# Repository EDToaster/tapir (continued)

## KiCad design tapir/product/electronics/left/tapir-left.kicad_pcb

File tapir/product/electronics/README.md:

# Tapir Rev A | electrical handoff

Open `left/tapir-left.kicad_pro` and `right/tapir-right.kicad_pro` separately in **KiCad 10.0.8**. These are physically distinct two-layer carriers, not the same PCB flipped over. The native schematics, boards, editable libraries, component STEP files and local tables live together here. Nothing in this directory is a purchase, fabrication or assembly authorization.

## What is on the carrier

| Circuit | Left | Right | Electrical contract |
|---|---:|---:|---|
| SW1–21 + D1–21 | 21 | 21 | Direct-solder Kailh CPG135001D01. P1 = column, P2 = corresponding diode anode; diode pad 1/cathode returns to ROW. One diode per physical switch. |
| SW22–24 + D22–24 | 3 | 0 | PTS810SJM250SMTR LFS. R3C0 = left click; R3C1 = scroll hold; R3C2 = right click. Thumb keys remain R3C3/4/5, outer to inner. |
| U1 | 1 | 1 | [Seeed XIAO nRF52840 Plus, non-Sense](https://www.seeedstudio.com/Seeed-Studio-XIAO-nRF52840-Plus-p-6359.html), 102010672. Surface-mount the module, including its underside pads. Header-mounted or non-Plus boards do not implement this carrier. |
| J1, S1 | 1 each | 1 each | [Protected 100 mAh pack](https://www.adafruit.com/product/1570); factory PH termination, no cutting or battery soldering. J1.1 = CELL_PLUS, J1.2 = GND. S1.2 = cell, S1.1 = VBAT_SW, S1.3 = isolated. |
| U2, C1, C2, R1–R3, J2 | 0 | 1 each | [Active-high TPS22918DBVR](https://www.ti.com/product/TPS22918) switches the pointer's 3.3 V rail. The Sprintek driver and head are an **off-board harness assembly**, not fake components placed on the main PCB. |

Every switch row uses the same scan polarity. Local columns run outer to inner on both hands; firmware reverses the right physical column order when forming the Corne logical layout. The matrix path is COL → switch → diode A → diode K → ROW. The left mouse controls are physical, diode-isolated inputs, not overloaded key combinations.

### Module interface

| Carrier U1 pads | Module pins | Use |
|---|---|---|
| 1, 2, 3, 4 | D0…D3 | ROW0…ROW3 |
| 5, 6, 7, 8, 9, 10 | D4…D9 | COL0…COL5 |
| 11, 15, 16, 17 | D10/P1.15, D11/P0.15, D12/P0.19, D13/P1.01 | Right: PS2_DATA, PS2_CLK, PS2_RST, PTR_EN. Left: intentionally unused. |
| 12, 13, 14 | 3V3, ground, VBUS | U1.12 supplies only the right pointer circuit. No carrier VBUS load; USB data, ESD, connector and charger are on U1. |
| 18–23 | D14…D19 | All intentionally unused. D14/15 are shared with NFC; D16 is a battery-sense pin. |
| 24, 25, 26, 27 | SWDIO, SWDCLK, nRESET, ground | First three are unused host pads; 27 is connected to carrier GND. Use the module button for recovery, removing the right bridge with the cell disconnected. No side-access SWD header is claimed. |
| 28, 29 | BAT+, BAT− | VBAT_SW and GND. These are invisible once the XIAO is installed: confirm land overlap, paste transfer and solder quality on a coupon/sample before accepting assembly. |

Numbering is the **host footprint**, not the GPIO number. The [Seeed Plus board artwork](https://files.seeedstudio.com/wiki/XIAO-BLE/Seeed_Studio_XIAO_nRF52840_Plus.zip), [host land pattern](https://files.seeedstudio.com/wiki/XIAO-KiCad-Library/New_XIAO_Series_Footprints.zip) and [Zephyr Plus pin table](https://docs.zephyrproject.org/latest/boards/seeed/xiao_nrf52840_plus/doc/index.html) are the basis. The host battery lands are not exactly centered on the module's actual rectangles: see `reports/xiao-hidden-lands.json` for the explicit geometry comparison. That is a land-overlap audit, not inspection of a solder joint.

### Power and pointing assembly

S1 disconnects **the cell**, not USB. Switch open + cable attached means the MCU can still run and the cell cannot charge. With S1 closed the module's onboard charger is connected to the cell. Do not fit an additional charger or assume that the mere presence of pack protection makes an unknown charge setting safe. [Seeed specifies high-impedance P0.13 without pulls for approximately 50 mA](https://wiki.seeedstudio.com/XIAO_BLE/); check every bootloader/application startup path and measure cell current before unattended use. The [1570 pack drawing and electrical limits](https://cdn-shop.adafruit.com/product-files/1570/1570datasheet.pdf) take precedence over marketing dimensions.

**Check polarity before mating the real cell.** In the [Adafruit Feather M0 rev C PCB](https://github.com/adafruit/Adafruit-Feather-M0-Basic-Proto-PCB/blob/master/Adafruit%20Feather%20M0%20Basic%20rev%20C.brd), X1 pad 2 is VBAT and pad 1 is ground. Its Eagle XY and mating orientation differ from the [KiCad JST footprint](https://gitlab.com/kicad/libraries/kicad-footprints/-/blob/10.0.8/Connector_JST.pretty/JST_PH_S2B-PH-SM4-TB_1x02-1MP_P2.00mm_Horizontal.kicad_mod): align the **physical mating faces**, not printed pad numbers. In Tapir the left native pad (−1,−2.85) is +, the right pad (+1,−2.85) is −. Confirm the actual pack with a meter at its unplugged housing, then continuity from an unpowered mated dummy pigtail through J1/S1 to U1 pads 28/29. Do not probe by shorting adjacent live contacts. Do not connect anything if these checks disagree.

Right J2 is a row of five wire terminations, not an 8-pin FFC footprint. Read the actual **Method 1 castellated** pin-1 mark on the [Sprintek SK8707-01-004 drawing, pages 3–4](https://docs.holykeebs.com/datasheets/SK8707-01.pdf#page=3). Do not use the pin numbering of either FFC alternative.

| J2 → Sprintek Method 1 | Signal | Expected |
|---|---|---|
| 1 → 1 | GND | Common return; square pad marks carrier pin 1. |
| 2 → 2 | PS2_DATA | Open drain; 4.7 kΩ to PTR_3V3, never to unswitched 3V3. |
| 3 → 3 | PS2_CLK | Same pull-up scheme; no pull-ups enabled from the MCU when off. |
| 4 → 4 | PS2_RST | Active high. Hold low or release as appropriate; never drive high with driver VCC off. |
| 5 → 5 | PTR_3V3 | U2.6. U2.5 QOD is tied here to discharge the rail. U2.4 CT is deliberately open; R3 100 kΩ defaults EN low. |
| None → 6,7,8 | Driver mouse inputs | Not wired to the carrier or left half. |

Keep the four raw sensor-to-driver connections separate from this five-wire host cable. Fit the original matched driver/head pair from the **3.3 V detached –004** kit; maintain sensor/driver matching marks and verified wiring order. If the kit is not already terminated, label both sides of each of the four wires from the supplied sensor/driver markings or vendor guidance; do not infer pin order from a generic donor or trace color. Do not power until checked. Keep sensor wires short and strain relieved, away from switch tails, the antenna and moving parts. Insulate driver solder joints from the carrier; the separate bridge must take pointing loads. Physical retention, reach, lead dress, calibration and assembled RSSI are prototype gates.

R1/R2 draw about 0.70 mA per line, but only while that line is low and the rail is enabled. The right driver itself draws a typical [2.09 mA active, 0.65 or 1.44 mA idle depending on Z-tap, and 40 µA in its power-down mode](https://docs.holykeebs.com/datasheets/SK8707-01.pdf#page=5). U2's 1 µF input / 0.1 µF local output is a 10:1 local ratio; the module's unknown internal capacitance and cable add to the load. Scope turn-on droop, discharge, clock edges and leakage with the real assembly; do not convert these nominal figures into a measured keyboard runtime.

## Stackup, drawings and gates

Target standard **2-layer FR-4, finished 1.6 mm, 1 oz outer copper, ENIG, tented vias**; no impedance-controlled bus is routed on the carrier. Nominal signal traces are 0.20 mm, power/ground 0.30 mm, copper spacing at least 0.20 mm, copper to routed edge 0.30 mm, copper to unrelated drilled holes 0.25 mm. Through vias are 0.60/0.30 mm (signal) or 0.65/0.30 mm (power); carrier-mount NPTHs are Ø2.20 mm with Ø5.40 keepouts. These are design targets, not a board-house quote; recheck the [JLCPCB rigid production capabilities](https://jlcpcb.com/capabilities/pcb-capabilities/) and actual stack/finish/tolerance at release. Solder/paste process, panel rails, tool access, registration, coupon and drill compensation need fabrication review.

Do not mirror any offset a second time. In the PCB editor each hand uses `XY = geometry.XY + (100,100) mm`, and clockwise geometry angles become negative KiCad angles. The vendor XIAO's native USB points +X, so its exception is `rotation = 90° − geometry.a`. `step/tapir-<hand>-populated.step` uses a **100×100 mm user origin**; thus STEP XY = (geometry.x, −geometry.y) and the component seating plane is at STEP z = +1.595 mm. The exported dielectric solid is not the whole finished copper/mask stack. No detached module, bridge, battery, harness or case is pretended to exist on the native carrier STEP. See `models/` for real part versus independent fit-proxy status.

- **Electrical evidence:** `reports/tapir-<hand>-erc.json`, `...-drc.json`, `...-schematic-parity.json`, `...-routing.json`. Check report counts, `passes`, and that the board revision matches the report. Missing reports do not pass. The native DRC JSON records default advisory checks ignored by KiCad; no per-instance violations have been accepted as exclusions. Formal EDA checks cannot detect incorrect vendor pin interpretation, poor soldering, back-power, wrong firmware behavior or RF detuning.
- **Manufacturing review:** `build/fabrication/<hand>/` contains review-only Gerber X2 copper/mask/paste/silk/edge layers, separate NPTH/PTH Excellon files, drill report, machine placement/board BOM CSVs, native human-readable ERC/DRC and SHA-256 manifest. Inspect layer registration, drill classification and pin 1 by eye in an independent viewer before seeking purchase approval. Do not upload straight to checkout.
- **Library provenance:** local stock patterns are adapted from KiCad 10.0.8 (model paths localized; PCM12 actuator silk moved to assembly so it is not clipped by the edge). Stock patterns retain [KiCad's CC BY-SA 4.0 + design exception](https://www.kicad.org/libraries/license/index.html); license text is under `models/licenses/`. Seeed supplies the non-Sense Plus land pattern [in its hardware library](https://files.seeedstudio.com/wiki/XIAO-KiCad-Library/New_XIAO_Series_Footprints.zip), adapted here by removing unrelated alternate model bindings and moving outline ink to Fab. No blanket KiCad license is asserted over Seeed CAD. The original physical switch pattern references [Kailh's selected part specification](https://cdn-shop.adafruit.com/product-files/5113/CHOC+keyswitch_Kailh-CPG135001D01_C400229.pdf) and [Ergogen's solder-in Choc contact arrangement](https://github.com/ergogen/ergogen/blob/develop/src/footprints/choc.js). J2 and M2 fixtures are project-specific. Check each local model's separate credits.

## Rebuild and use

For routine KiCad edits open the native sources; generators are optional. When regenerating from a changed design, work in a disposable checkout and preserve the routed source until a candidate passes all checks:

```sh
cd product/electronics
python3 tools/design.py                       # hand circuit manifests in build/
/usr/bin/python3 tools/place_board.py          # unrouted boards in build/<hand>
python3 tools/schematic.py                     # see tools/schematic.md
# Native schematic and routing workflows:
# tools/schematic.md and tools/route.md (includes pinned local router JARs).
/usr/bin/python3 tools/route_finish.py left right  # replay bundled SES, test before and after ground fill
/usr/bin/python3 tools/route_verify.py left right
python3 -m venv /tmp/tapir-cam && /tmp/tapir-cam/bin/pip install gerbonara==1.6.3
export TAPIR_CAM_PYTHON=/tmp/tapir-cam/bin/python
python3 tools/export_handoff.py left
python3 tools/export_handoff.py right
```

For a deliberate library refresh run `python3 tools/footprints.py /path/to/New_XIAO_Series_Footprints.zip`; the vendor ZIP hash is pinned. Board object UUIDs or timestamps can change on regeneration: manufacturing comparison must examine geometry, nets, layers, rules and fresh native reports, not timestamps. Never overwrite a hand-routed ECO merely to refresh documentation.

The shipped routes replay without a JAR, JVM or network once prerequisites are installed. Each hand has fixed tracks (including a GND path), GND zones on both copper layers, and an antenna exclusion for those zones. The export verifies the board hash, reruns native all-severity ERC/DRC/parity, and independently reopens its own RS-274X/X2 and Excellon output with Gerbonara. Read `build/fabrication/<hand>/cam-readback.json`: every numbered copper land on each layer, complete drill register and profile centerline must agree. Gerbonara may note KiCad's placement of G90 after the header; it still decodes the absolute coordinates, which are compared against native pads and vias. The KiCad Gerber Job file does not encode a selected surface finish; ENIG is a **manual** order/checklist requirement, not an implied order option.

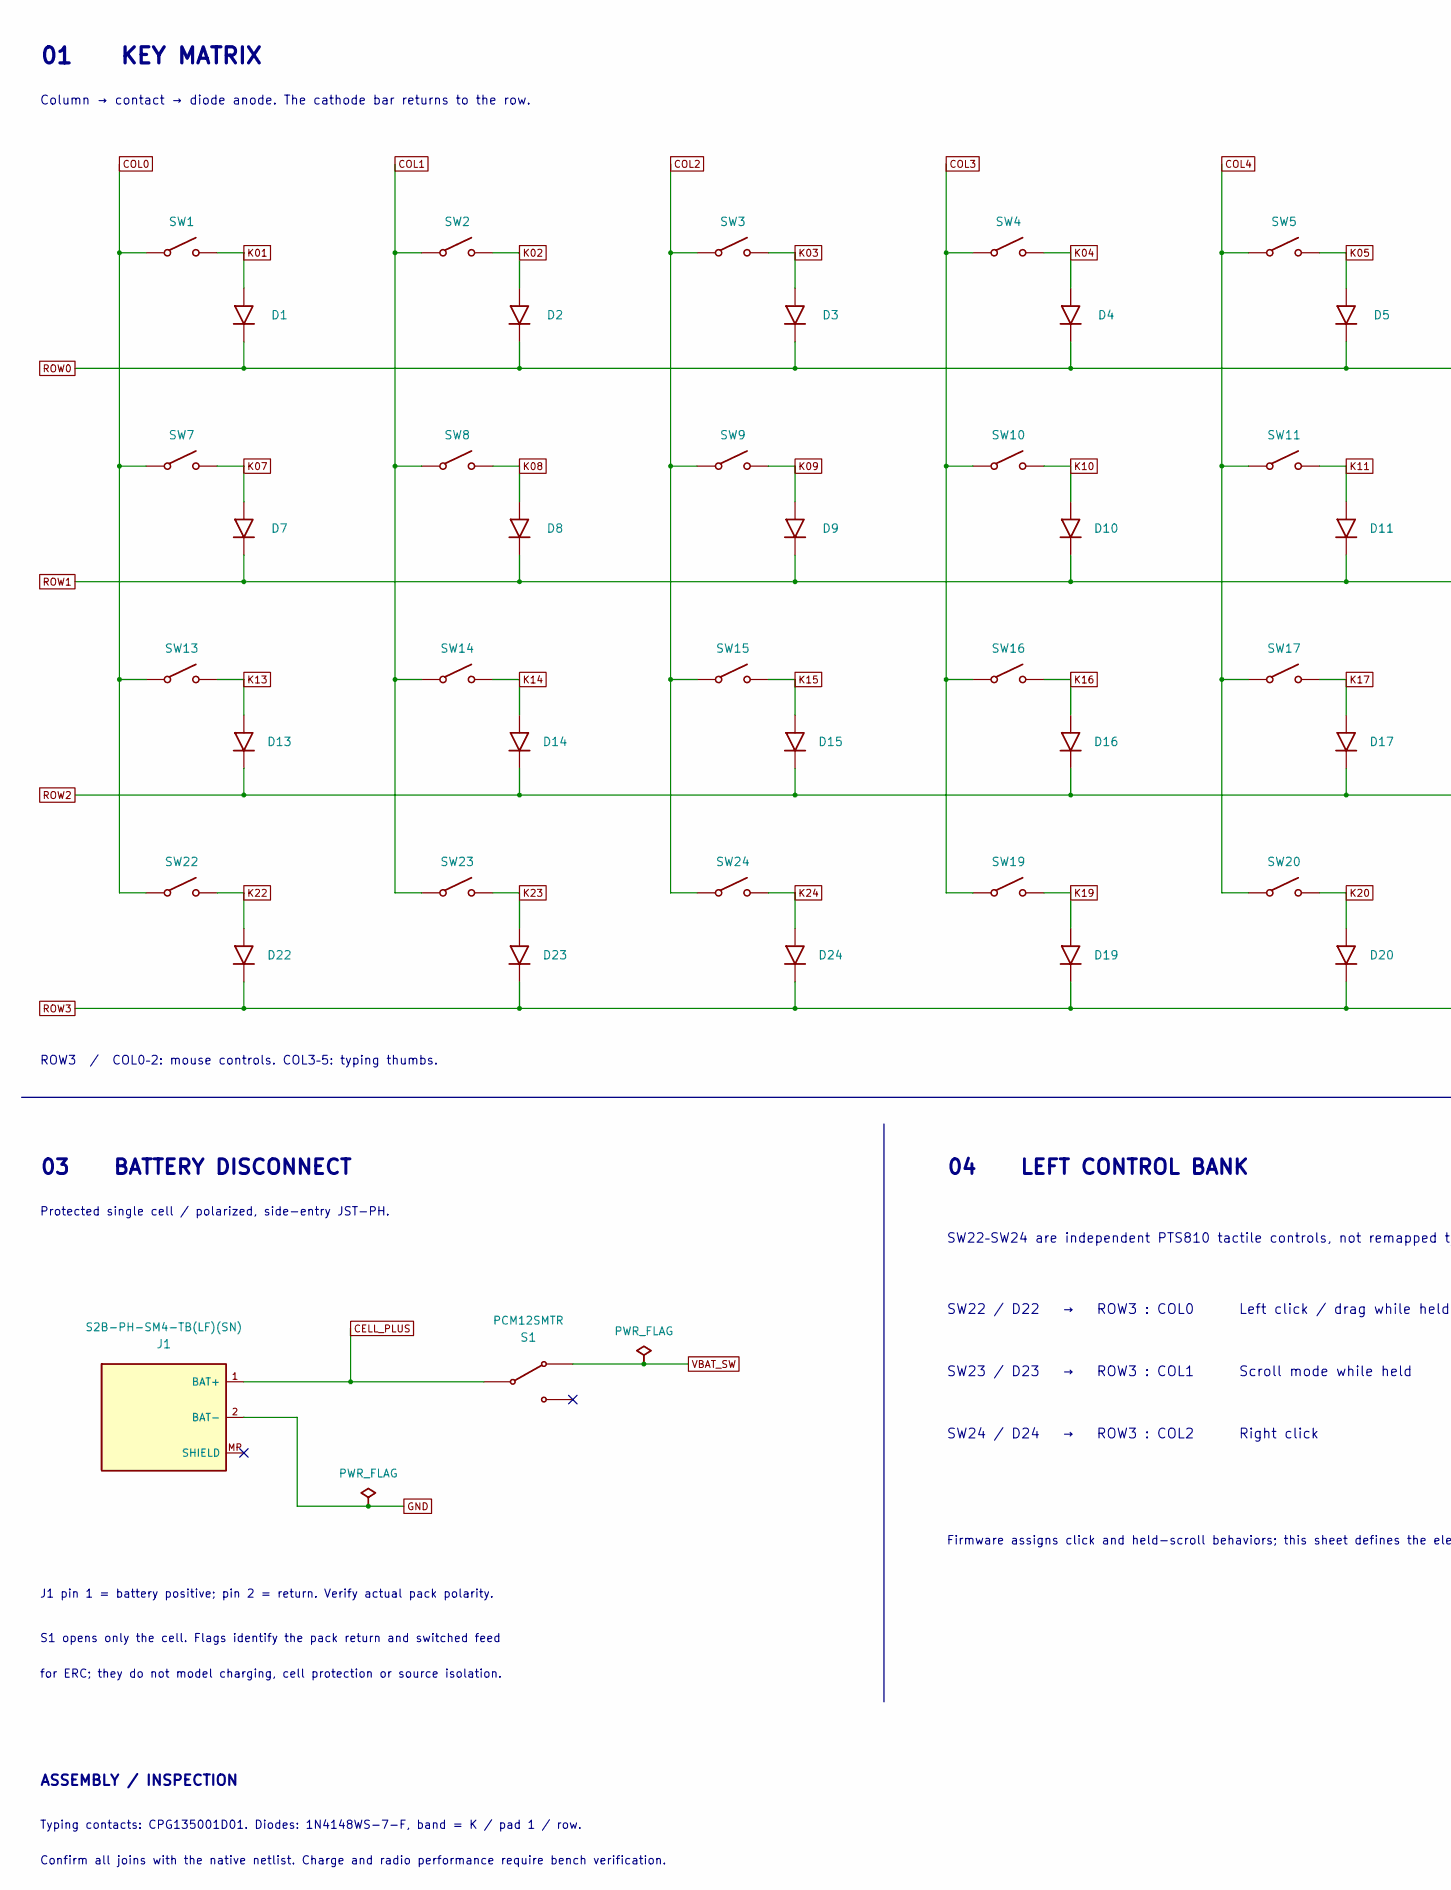
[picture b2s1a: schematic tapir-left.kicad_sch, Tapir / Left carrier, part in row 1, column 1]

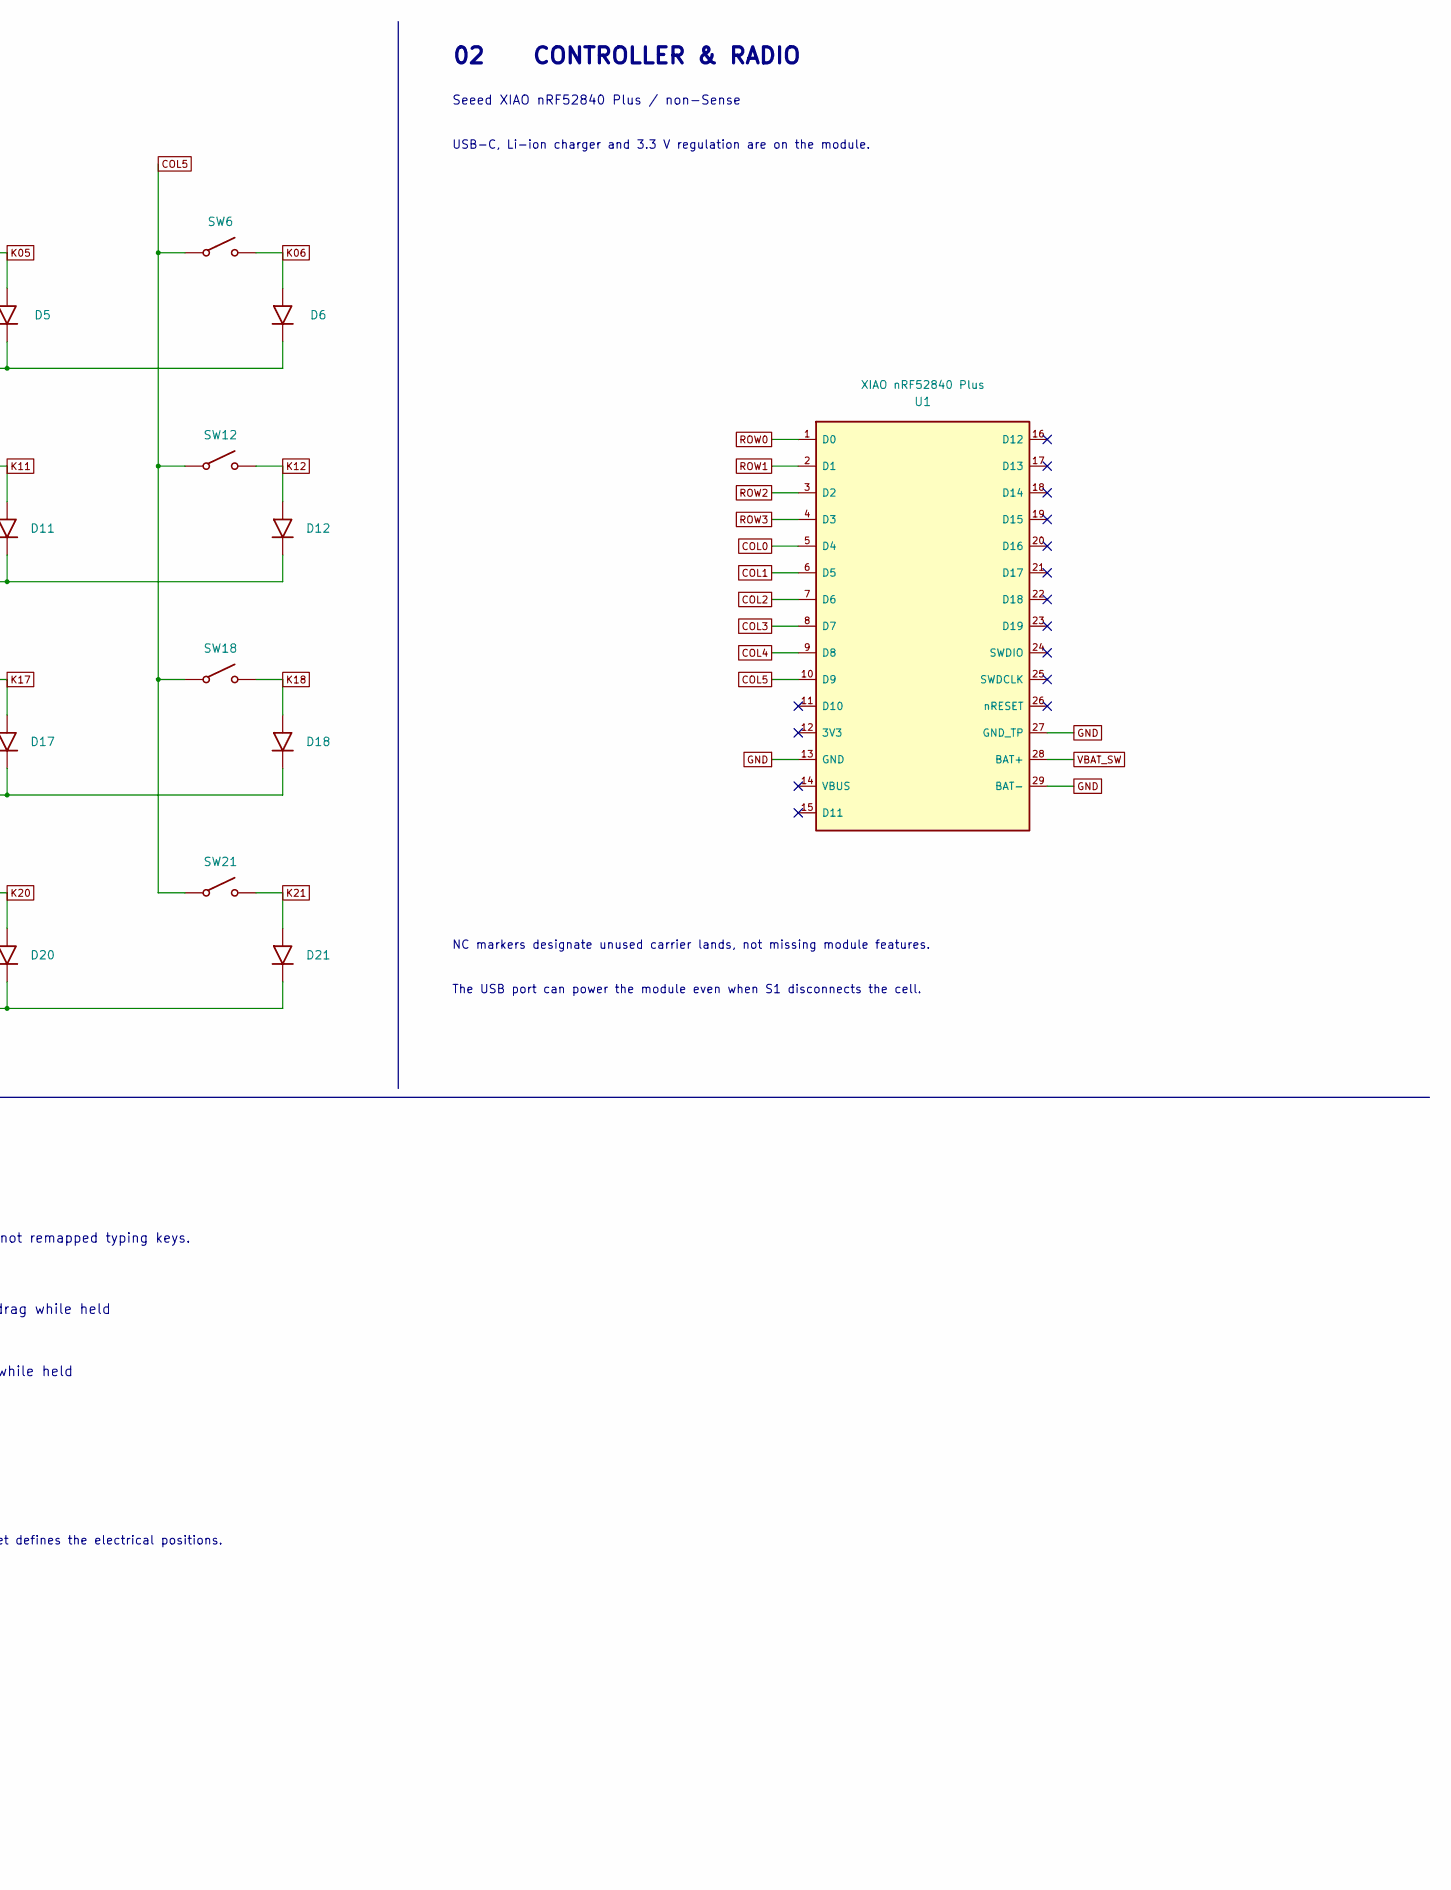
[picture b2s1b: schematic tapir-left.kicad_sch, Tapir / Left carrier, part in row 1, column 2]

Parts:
D1, D2, D3, D4, D5, D6, D7, D8, D9, D10, D11, D12, D13, D14, D15, D16, D17, D18, D19, D20, D21, D22, D23, D24: 1N4148WS-7-F; D_SOD-323
J1: S2B-PH-SM4-TB(LF)(SN); JST_PH_S2B-PH-SM4-TB_1x02-1MP_P2.00mm_Horizontal
S1: PCM12SMTR; SW_SPDT_PCM12
SW1, SW2, SW3, SW4, SW5, SW6, SW7, SW8, SW9, SW10, SW11, SW12, SW13, SW14, SW15, SW16, SW17, SW18, SW19, SW20, SW21: CPG135001D01; Choc_PG1350
SW22, SW23, SW24: PTS810SJM250SMTR LFS; SW_SPST_PTS810
U1: XIAO nRF52840 Plus; XIAO-nRF52840-Plus-SMD

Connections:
CELL_PLUS: J1.1 (BAT+), S1.2 (COM)
COL0: SW1.1, SW7.1, SW13.1, SW22.1, U1.5 (D4)
COL1: SW2.1, SW8.1, SW14.1, SW23.1, U1.6 (D5)
COL2: SW3.1, SW9.1, SW15.1, SW24.1, U1.7 (D6)
COL3: SW4.1, SW10.1, SW16.1, SW19.1, U1.8 (D7)
COL4: SW5.1, SW11.1, SW17.1, SW20.1, U1.9 (D8)
COL5: SW6.1, SW12.1, SW18.1, SW21.1, U1.10 (D9)
GND: J1.2 (BAT-), U1.13 (GND), U1.27 (GND_TP), U1.29 (BAT-)
K01: D1.2 (A), SW1.2
K02: D2.2 (A), SW2.2
K03: D3.2 (A), SW3.2
K04: D4.2 (A), SW4.2
K05: D5.2 (A), SW5.2
K06: D6.2 (A), SW6.2
K07: D7.2 (A), SW7.2
K08: D8.2 (A), SW8.2
K09: D9.2 (A), SW9.2
K10: D10.2 (A), SW10.2
K11: D11.2 (A), SW11.2
K12: D12.2 (A), SW12.2
K13: D13.2 (A), SW13.2
K14: D14.2 (A), SW14.2
K15: D15.2 (A), SW15.2
K16: D16.2 (A), SW16.2
K17: D17.2 (A), SW17.2
K18: D18.2 (A), SW18.2
K19: D19.2 (A), SW19.2
K20: D20.2 (A), SW20.2
K21: D21.2 (A), SW21.2
K22: D22.2 (A), SW22.2
K23: D23.2 (A), SW23.2
K24: D24.2 (A), SW24.2
ROW0: D1.1 (K), D2.1 (K), D3.1 (K), D4.1 (K), D5.1 (K), D6.1 (K), U1.1 (D0)
ROW1: D7.1 (K), D8.1 (K), D9.1 (K), D10.1 (K), D11.1 (K), D12.1 (K), U1.2 (D1)
ROW2: D13.1 (K), D14.1 (K), D15.1 (K), D16.1 (K), D17.1 (K), D18.1 (K), U1.3 (D2)
ROW3: D19.1 (K), D20.1 (K), D21.1 (K), D22.1 (K), D23.1 (K), D24.1 (K), U1.4 (D3)
VBAT_SW: S1.1 (ON), U1.28 (BAT+)

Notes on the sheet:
01 KEY MATRIX
Column → contact → diode anode. The cathode bar returns to the row.
ROW3 / COL0–2: mouse controls. COL3–5: typing thumbs.
02 CONTROLLER & RADIO
Seeed XIAO nRF52840 Plus / non-Sense
USB-C, Li-ion charger and 3.3 V regulation are on the module.
NC markers designate unused carrier lands, not missing module features.
The USB port can power the module even when S1 disconnects the cell.
03 BATTERY DISCONNECT
Protected single cell / polarized, side-entry JST-PH.
J1 pin 1 = battery positive; pin 2 = return. Verify actual pack polarity.
S1 opens only the cell. Flags identify the pack return and switched feed
for ERC; they do not model charging, cell protection or source isolation.
ASSEMBLY / INSPECTION
Typing contacts: CPG135001D01. Diodes: 1N4148WS-7-F, band = K / pad 1 / row.
Confirm all joins with the native netlist. Charge and radio performance require bench verification.
04 LEFT CONTROL BANK
SW22–SW24 are independent PTS810 tactile controls, not remapped typing keys.
SW22 / D22 → ROW3 : COL0 Left click / drag while held
SW23 / D23 → ROW3 : COL1 Scroll mode while held
SW24 / D24 → ROW3 : COL2 Right click
Firmware assigns click and held-scroll behaviors; this sheet defines the electrical positions.

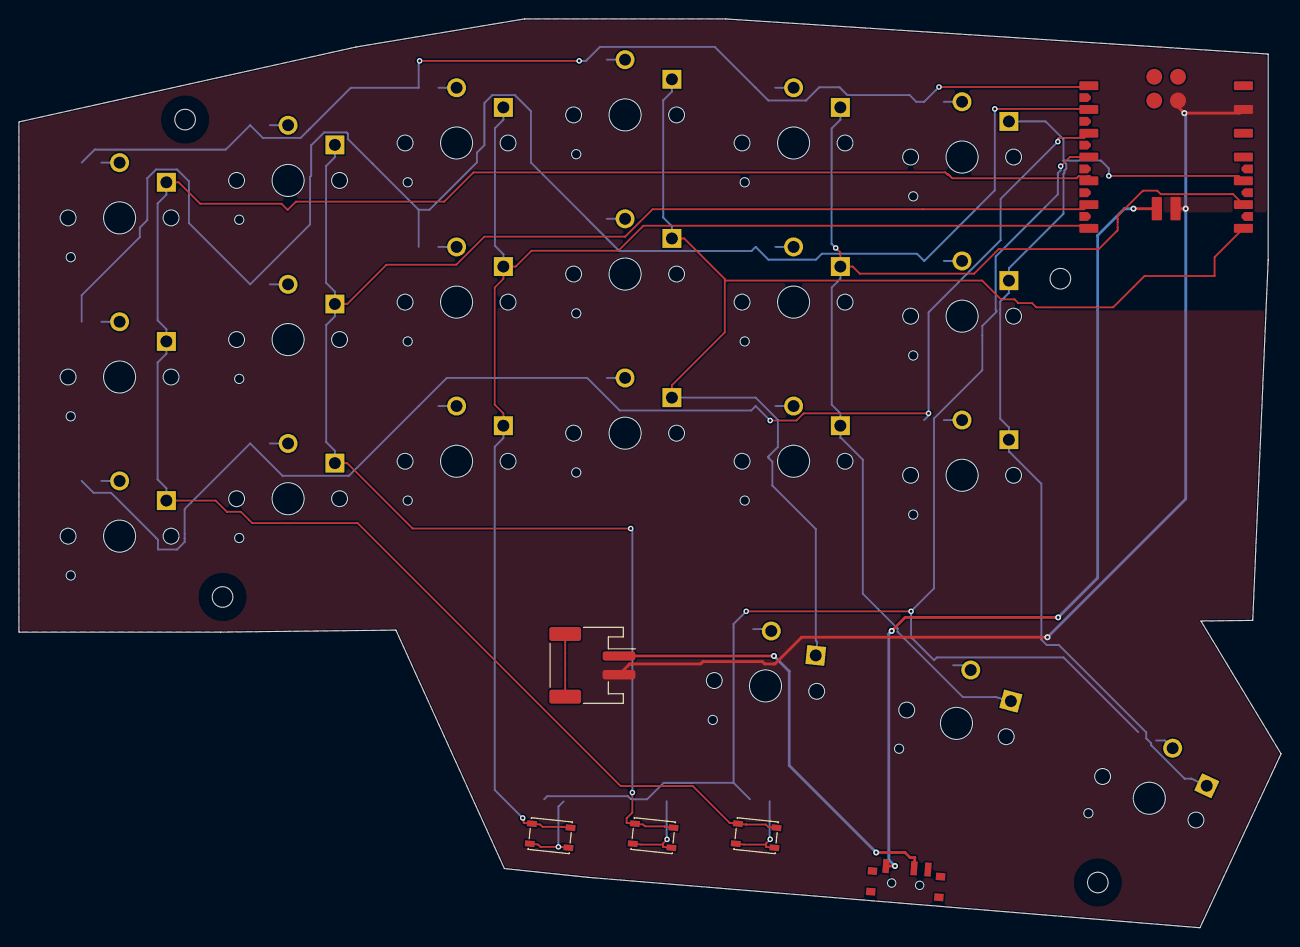
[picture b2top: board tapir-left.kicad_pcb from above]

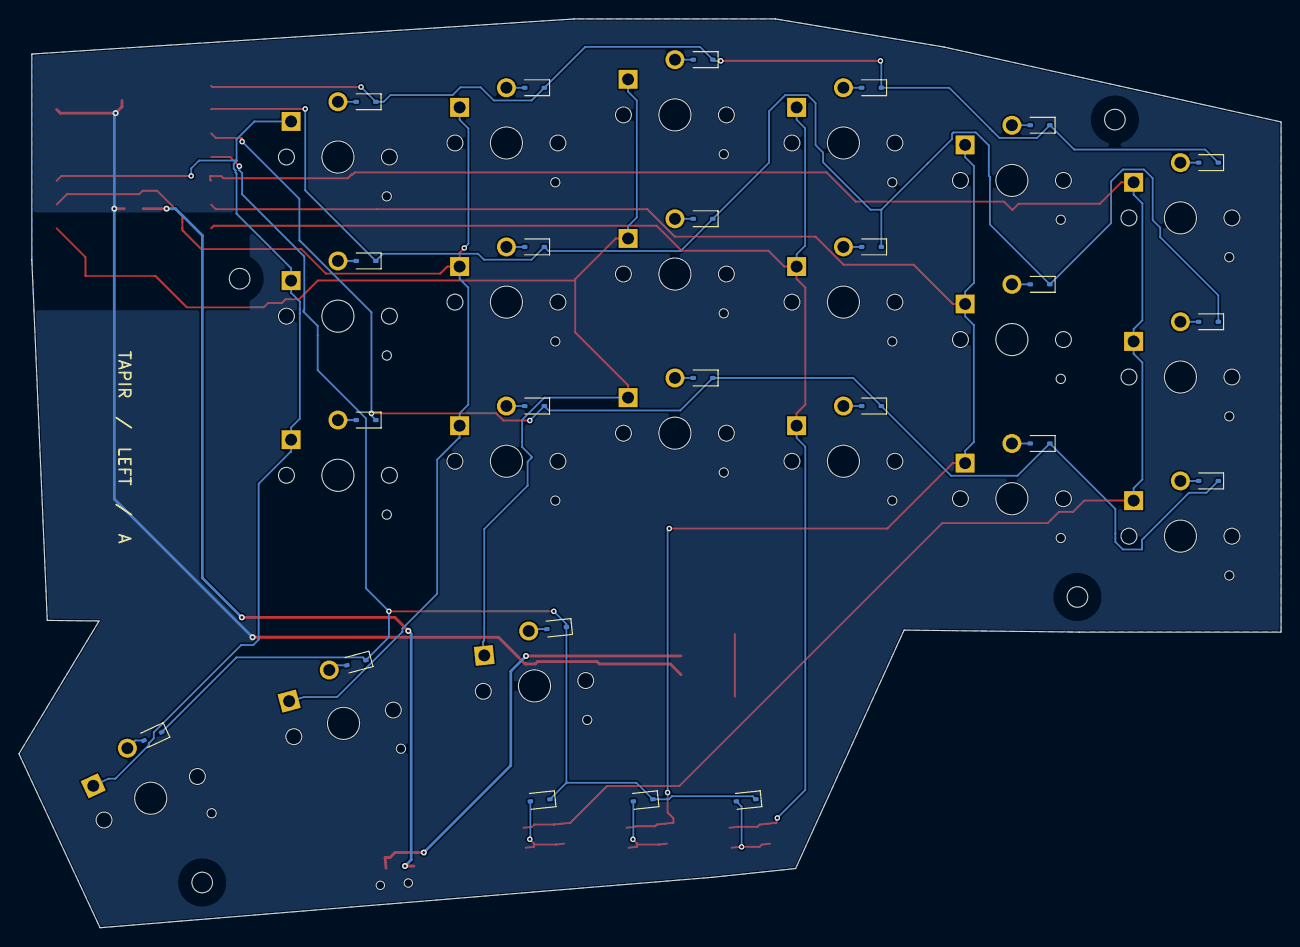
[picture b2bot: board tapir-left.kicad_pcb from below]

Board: 2 copper layers, 134.8 x 97.1 mm, 55 parts (24 on the bottom side), 37 nets.

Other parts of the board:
H1, H2, H3, H4: M2_Carrier_Mount
